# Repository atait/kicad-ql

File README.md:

# KiCad QuickLook

Press Space on a KiCad board (`.kicad_pcb`), footprint (`.kicad_mod`) or schematic (`.kicad_sch`) in
Finder to see a preview.
KiCad doesn't need to be installed.

## Using it

- **Zoom**: pinch, or use the mouse wheel.
- **Pan**: scroll with two fingers, or click and drag.
- **Fit to window**: double-tap with two fingers.
- **Open in KiCad**: double-click or Cmd+O.

**Boards:** click a layer in the legend to bring it to the front. Click it again to see all layers.
**View from back** shows the board from the bottom, mirrored.

**Footprints:** shown like a board, without the back view. The legend also has the fab, solder mask
and Edge.Cuts layers, each pad is labelled with its number, and silkscreen is drawn dark.

**Schematics:** the sheet is drawn in KiCad's colours. Zoom in to read small text. For a hierarchical
design, the top sheet shows each sub-sheet as a box. To see what's inside, preview the sub-sheet's own
file.

The preview is an overview, not a replacement for KiCad. It uses the system font rather than KiCad's.

## Install

1. Download `KiCadQL.zip` from the [Releases](../../releases) page and unzip it.
2. Move `KiCadQL.app` to your Applications folder and open it once. You can quit it straight away.
3. If previews don't appear, turn on *KiCad PCB Preview* in System Settings ▸ General ▸ Login Items &
   Extensions ▸ Quick Look.

Requires macOS 14 or later.

## Building from source

See [docs/XCODE.md](docs/XCODE.md). To try the renderer without Xcode:

```sh
swift run -c release --package-path KiCadPCBKit kiql-render examples/LoomRide-v1.kicad_pcb out.png 1200
swift run -c release --package-path KiCadPCBKit kiql-render examples/SkySense-bank.kicad_sch out.png 2000
swift run -c release --package-path KiCadPCBKit kiql-render examples/Crystal_HC49-U-3Pin_Vertical.kicad_mod out.png 1200
swift test --package-path KiCadPCBKit
```

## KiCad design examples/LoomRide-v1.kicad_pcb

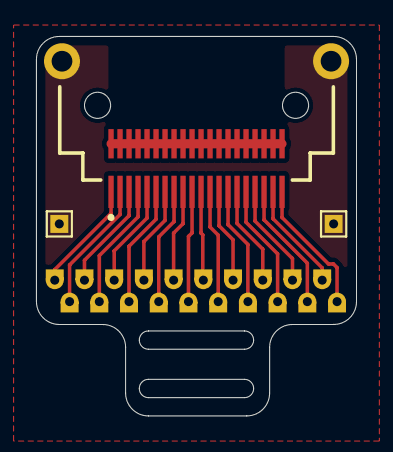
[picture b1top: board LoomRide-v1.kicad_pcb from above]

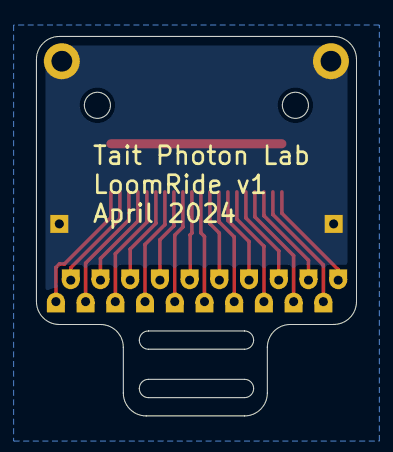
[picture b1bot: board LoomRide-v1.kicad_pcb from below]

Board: 2 copper layers, 17.8 x 21.1 mm, 23 parts (20 on the bottom side), 22 nets.

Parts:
J1: Conn_02x20_Odd_Even_Shielded; LSHM-120-01-L-DH-A-S
TP1, TP2, TP3, TP4, TP5, TP6, TP7, TP8, TP9, TP10, TP11, TP12, TP13, TP14, TP15, TP16, TP17, TP18, TP19, TP20: TestPoint; WirePoint
TP21, TP22: TestPoint; TestPoint_THTPad_1.0x1.0mm_Drill0.5mm

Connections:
GND: J1.SH (Shield), TP21.1, TP22.1
unnamed: J1.1, TP1.1
unnamed: J1.3, TP2.1
unnamed: J1.5, TP3.1
unnamed: J1.7, TP4.1
unnamed: J1.9, TP5.1
unnamed: J1.2, J1.4, J1.6, J1.8, J1.10, J1.12, J1.14, J1.16, J1.18, J1.20, J1.22, J1.24, J1.26, J1.28, J1.30, J1.32, J1.34, J1.36, J1.38, J1.40
unnamed: J1.11, TP6.1
unnamed: J1.13, TP7.1
unnamed: J1.15, TP8.1
unnamed: J1.17, TP9.1
unnamed: J1.19, TP10.1
unnamed: J1.21, TP11.1
unnamed: J1.23, TP12.1
unnamed: J1.25, TP13.1
unnamed: J1.27, TP14.1
unnamed: J1.29, TP15.1
unnamed: J1.31, TP16.1
unnamed: J1.33, TP17.1
unnamed: J1.35, TP18.1
unnamed: J1.37, TP19.1
unnamed: J1.39, TP20.1

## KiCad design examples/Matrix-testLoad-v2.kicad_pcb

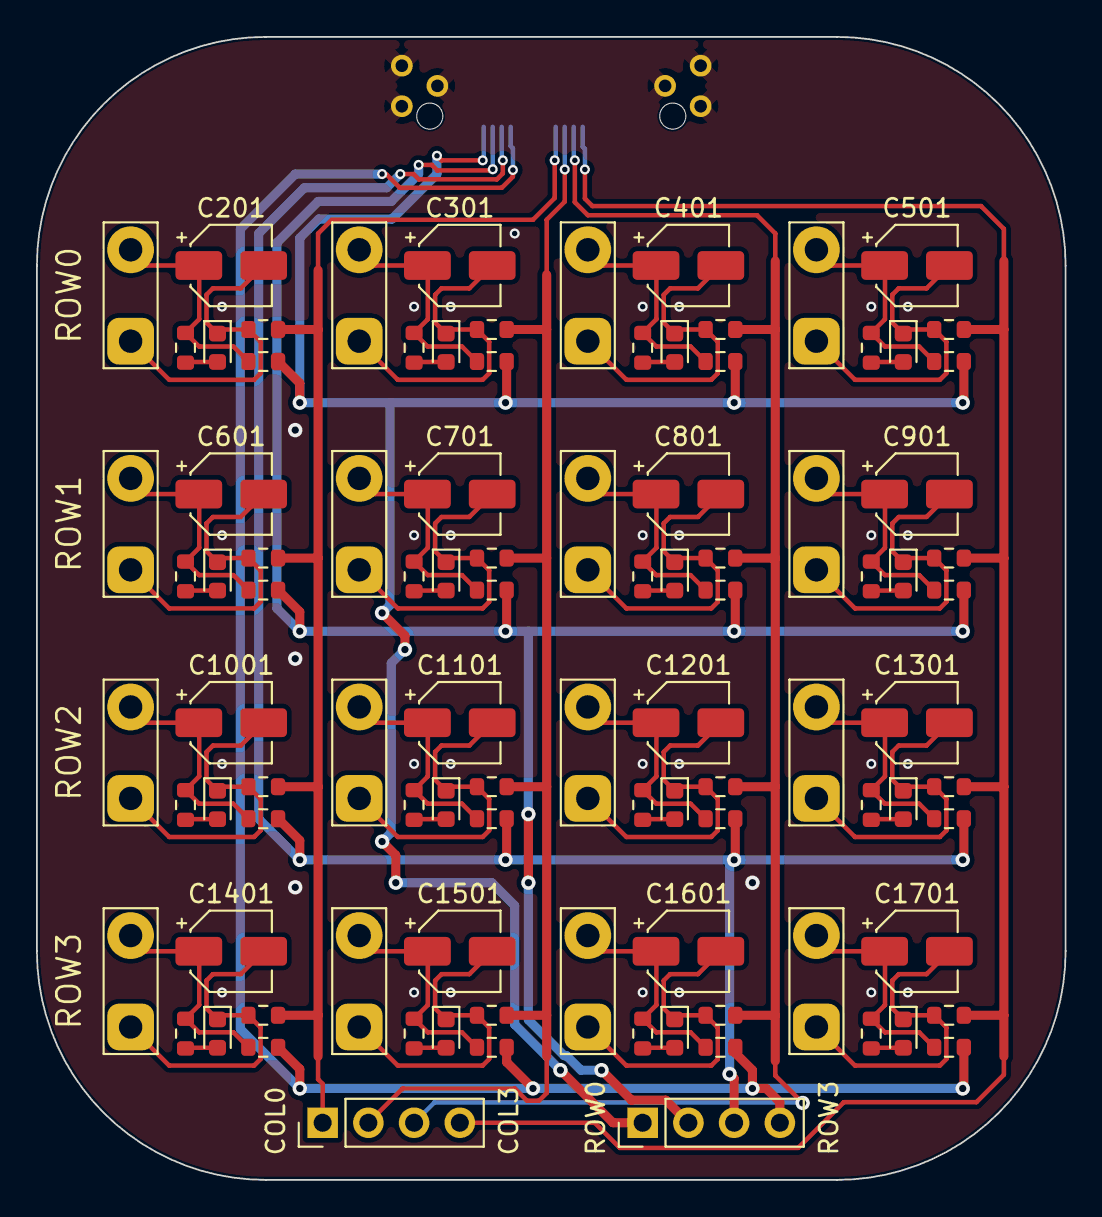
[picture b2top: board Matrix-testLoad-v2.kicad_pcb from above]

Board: 2 copper layers, 57.1 x 63.5 mm, 99 parts (1 on the bottom side), 57 nets.

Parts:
C201, C301, C401, C501, C601, C701, C801, C901, C1001, C1101, C1201, C1301, C1401, C1501, C1601, C1701: C_Polarized_US; CP_Elec_4x3
D201, D301, D401, D501, D601, D701, D801, D901, D1001, D1101, D1201, D1301, D1401, D1501, D1601, D1701: LED; LED_0603_1608Metric
J101: Conn_02x20_Odd_Even_Shielded; LSHM-120-01-L-RH-A-S
J102, J103: Conn_01x04_Pin; PinHeader_1x04_P2.54mm_Vertical
R201, R202, R203, R301, R302, R303, R401, R402, R403, R501, R502, R503, R601, R602, R603, R701, R702, R703, R801, R802, R803, R901, R902, R903, R1001, R1002, R1003, R1101, R1102, R1103, R1201, R1202, R1203, R1301, R1302, R1303, R1401, R1402, R1403, R1501, R1502, R1503, R1601, R1602, R1603, R1701, R1702, R1703: R_US; R_0603_1608Metric
TP202, TP302, TP402, TP502, TP602, TP702, TP802, TP902, TP1002, TP1102, TP1202, TP1302, TP1402, TP1502, TP1602, TP1702: TestPoint_2Pole; TestPoint_2Pads_Pitch5.08mm_Drill1.3mm

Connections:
/COL0: J101.21, J102.1, R201.1, R601.1, R1001.1, R1401.1
/COL1: J101.23, J102.2, R301.1, R701.1, R1101.1, R1501.1
/COL2: J101.25, J102.3, R401.1, R801.1, R1201.1, R1601.1
/COL3: J101.27, J102.4, R501.1, R901.1, R1301.1, R1701.1
/ROW0: J101.05 (Pin_5), J103.1, R203.1, R303.1, R403.1, R503.1
/ROW1: J101.07 (Pin_7), J103.2, R603.1, R703.1, R803.1, R903.1
/ROW2: J101.09 (Pin_9), J103.3, R1003.1, R1103.1, R1203.1, R1303.1
/ROW3: J101.11, J103.4, R1403.1, R1503.1, R1603.1, R1703.1
GND: J101.02 (Pin_2), J101.04 (Pin_4), J101.06 (Pin_6), J101.08 (Pin_8), J101.10, J101.12, J101.14, J101.16, J101.18, J101.20, J101.22, J101.24, J101.26, J101.28, J101.30, J101.32, J101.34, J101.36, J101.38, J101.40, J101.SH (Shield)
unnamed: C201.1, R202.1, R203.2, TP202.2
unnamed: C301.1, R302.1, R303.2, TP302.2
unnamed: C401.1, R402.1, R403.2, TP402.2
unnamed: C501.1, R502.1, R503.2, TP502.2
unnamed: C601.1, R602.1, R603.2, TP602.2
unnamed: C701.1, R702.1, R703.2, TP702.2
unnamed: C801.1, R802.1, R803.2, TP802.2
unnamed: C901.1, R902.1, R903.2, TP902.2
unnamed: C1001.1, R1002.1, R1003.2, TP1002.2
unnamed: C1101.1, R1102.1, R1103.2, TP1102.2
unnamed: C1201.1, R1202.1, R1203.2, TP1202.2
unnamed: C1301.1, R1302.1, R1303.2, TP1302.2
unnamed: C1401.1, R1402.1, R1403.2, TP1402.2
unnamed: C1501.1, R1502.1, R1503.2, TP1502.2
unnamed: C1601.1, R1602.1, R1603.2, TP1602.2
unnamed: C1701.1, R1702.1, R1703.2, TP1702.2
unnamed: D201.2 (A), R202.2
unnamed: C201.2, D201.1 (K), R201.2, TP202.1
unnamed: D301.2 (A), R302.2
unnamed: C301.2, D301.1 (K), R301.2, TP302.1
unnamed: D401.2 (A), R402.2
unnamed: C401.2, D401.1 (K), R401.2, TP402.1
unnamed: D501.2 (A), R502.2
unnamed: C501.2, D501.1 (K), R501.2, TP502.1
unnamed: D601.2 (A), R602.2
unnamed: C601.2, D601.1 (K), R601.2, TP602.1
unnamed: D701.2 (A), R702.2
unnamed: C701.2, D701.1 (K), R701.2, TP702.1
unnamed: D801.2 (A), R802.2
unnamed: C801.2, D801.1 (K), R801.2, TP802.1
unnamed: D901.2 (A), R902.2
unnamed: C901.2, D901.1 (K), R901.2, TP902.1
unnamed: D1001.2 (A), R1002.2
unnamed: C1001.2, D1001.1 (K), R1001.2, TP1002.1
unnamed: D1101.2 (A), R1102.2
unnamed: C1101.2, D1101.1 (K), R1101.2, TP1102.1
unnamed: D1201.2 (A), R1202.2
unnamed: C1201.2, D1201.1 (K), R1201.2, TP1202.1
unnamed: D1301.2 (A), R1302.2
unnamed: C1301.2, D1301.1 (K), R1301.2, TP1302.1
unnamed: D1401.2 (A), R1402.2
unnamed: C1401.2, D1401.1 (K), R1401.2, TP1402.1
unnamed: D1501.2 (A), R1502.2
unnamed: C1501.2, D1501.1 (K), R1501.2, TP1502.1
unnamed: D1601.2 (A), R1602.2
unnamed: C1601.2, D1601.1 (K), R1601.2, TP1602.1
unnamed: D1701.2 (A), R1702.2
unnamed: C1701.2, D1701.1 (K), R1701.2, TP1702.1

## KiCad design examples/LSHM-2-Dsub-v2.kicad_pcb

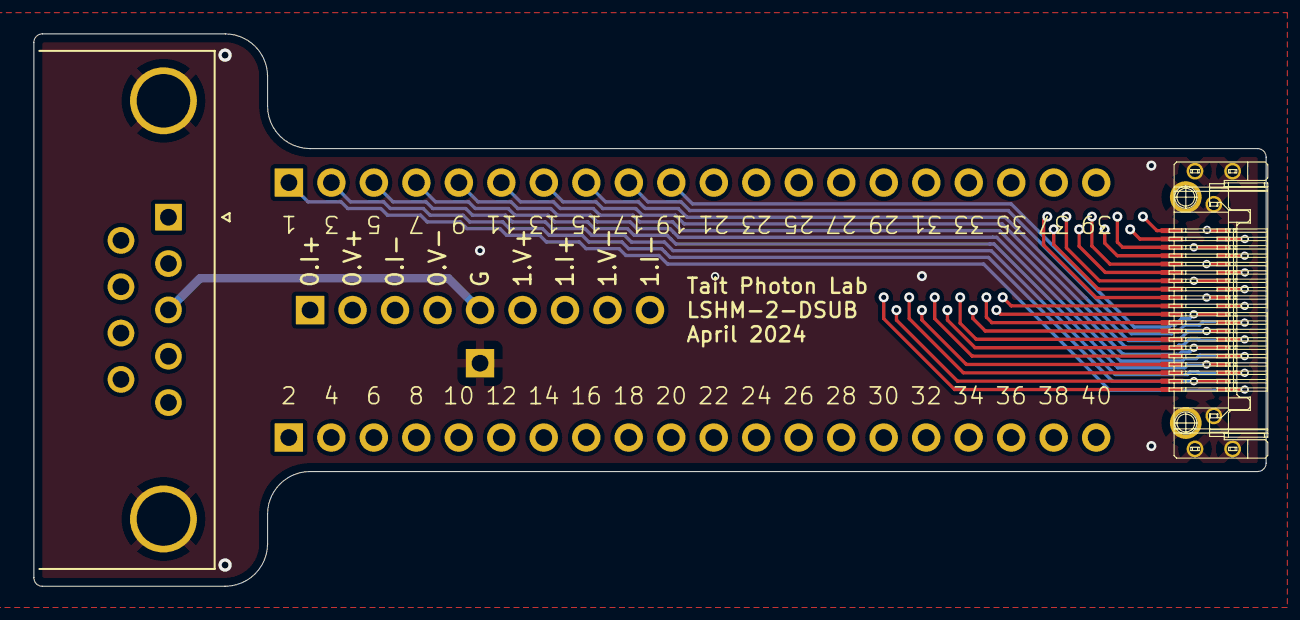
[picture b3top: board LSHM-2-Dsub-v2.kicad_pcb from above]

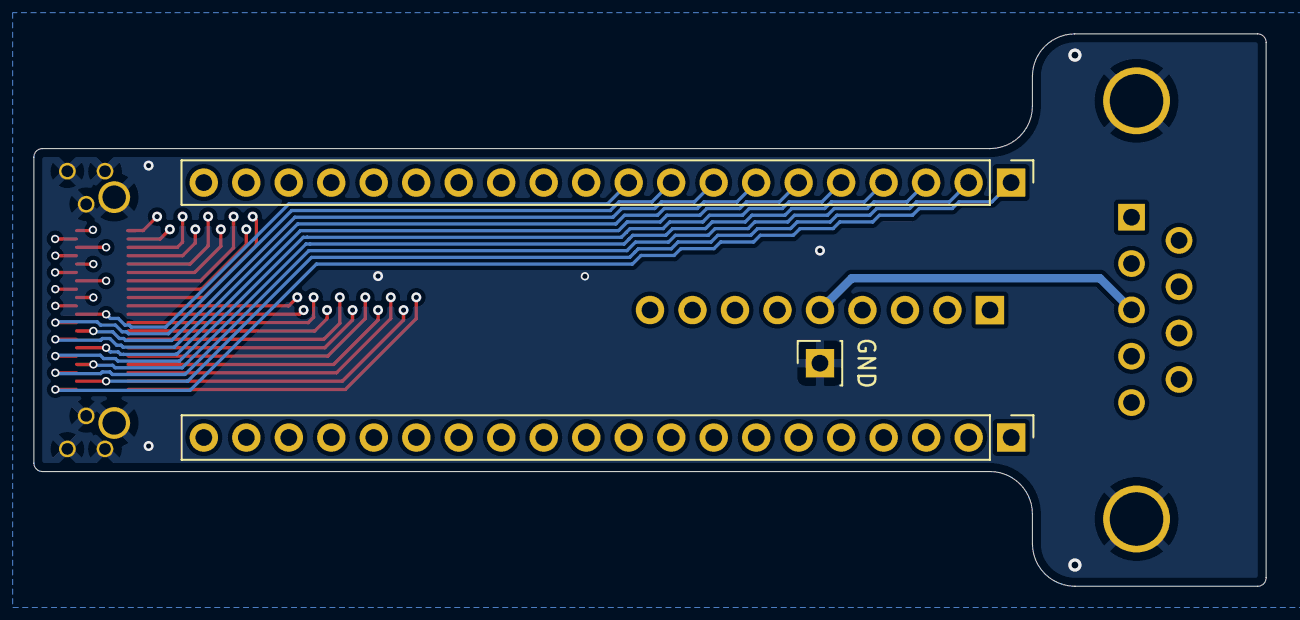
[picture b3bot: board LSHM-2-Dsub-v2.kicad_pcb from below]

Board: 4 copper layers, 73.7 x 33.0 mm, 6 parts (3 on the bottom side), 50 nets.

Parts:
J1, J3: Conn_01x20_Pin; PinHeader_1x20_P2.54mm_Vertical
J2: Conn_01x09_Pin; PinHeader_1x09_P2.54mm_Vertical
J5: Conn_02x20_Odd_Even_Shielded; LSHM-120-01-L-RH-A-S-TR
J8: GND; PinSocket_1x01_P2.54mm_Vertical
J9: DE9_Plug_MountingHoles; DSUB-9_Male_Horizontal_P2.77x2.84mm_EdgePinOffset4.94mm_Hou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

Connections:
/GGG: J2.5, J9.3
/TC0.I+: J2.1, J9.5
/TC0.I-: J2.3, J9.4
/TC0.V+: J2.2, J9.9
/TC0.V-: J2.4, J9.8
/TC1.I+: J2.7, J9.2
/TC1.I-: J2.9, J9.1
/TC1.V+: J2.6, J9.7
/TC1.V-: J2.8, J9.6
GND: J5.SH (Shield), J8.1, J9.0 (PAD)
unnamed: J1.1, J5.1
unnamed: J1.2, J5.3
unnamed: J1.3, J5.5
unnamed: J1.4, J5.7
unnamed: J1.5, J5.9
unnamed: J1.6, J5.11
unnamed: J1.7, J5.13
unnamed: J1.8, J5.15
unnamed: J1.9, J5.17
unnamed: J1.10, J5.19
unnamed: J1.11, J5.21
unnamed: J1.12, J5.23
unnamed: J1.13, J5.25
unnamed: J1.14, J5.27
unnamed: J1.15, J5.29
unnamed: J1.16, J5.31
unnamed: J1.17, J5.33
unnamed: J1.18, J5.35
unnamed: J1.19, J5.37
unnamed: J1.20, J5.39
unnamed: J3.1, J5.2
unnamed: J3.2, J5.4
unnamed: J3.3, J5.6
unnamed: J3.4, J5.8
unnamed: J3.5, J5.10
unnamed: J3.6, J5.12
unnamed: J3.7, J5.14
unnamed: J3.8, J5.16
unnamed: J3.9, J5.18
unnamed: J3.10, J5.20
unnamed: J3.11, J5.22
unnamed: J3.12, J5.24
unnamed: J3.13, J5.26
unnamed: J3.14, J5.28
unnamed: J3.15, J5.30
unnamed: J3.16, J5.32
unnamed: J3.17, J5.34
unnamed: J3.18, J5.36
unnamed: J3.19, J5.38
unnamed: J3.20, J5.40
